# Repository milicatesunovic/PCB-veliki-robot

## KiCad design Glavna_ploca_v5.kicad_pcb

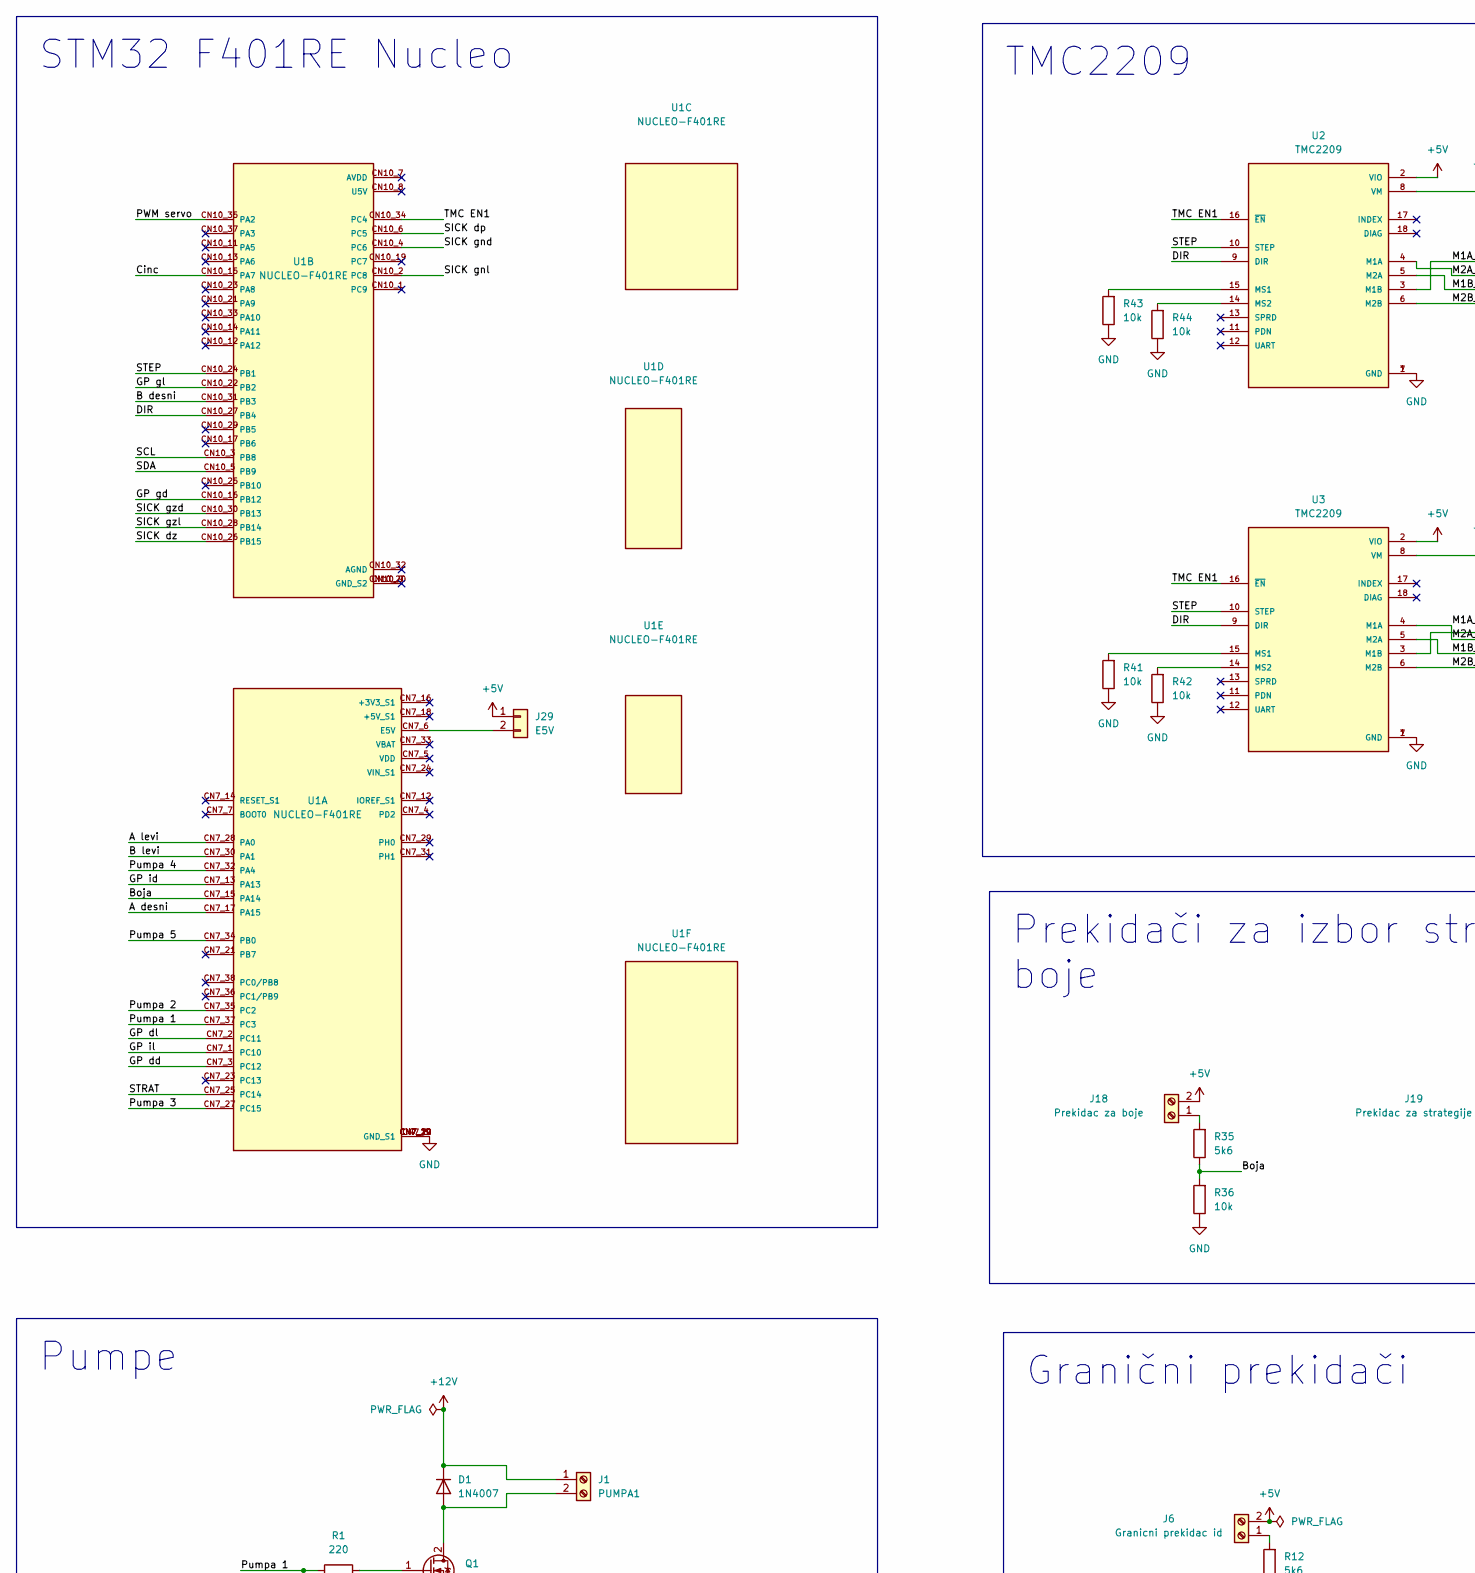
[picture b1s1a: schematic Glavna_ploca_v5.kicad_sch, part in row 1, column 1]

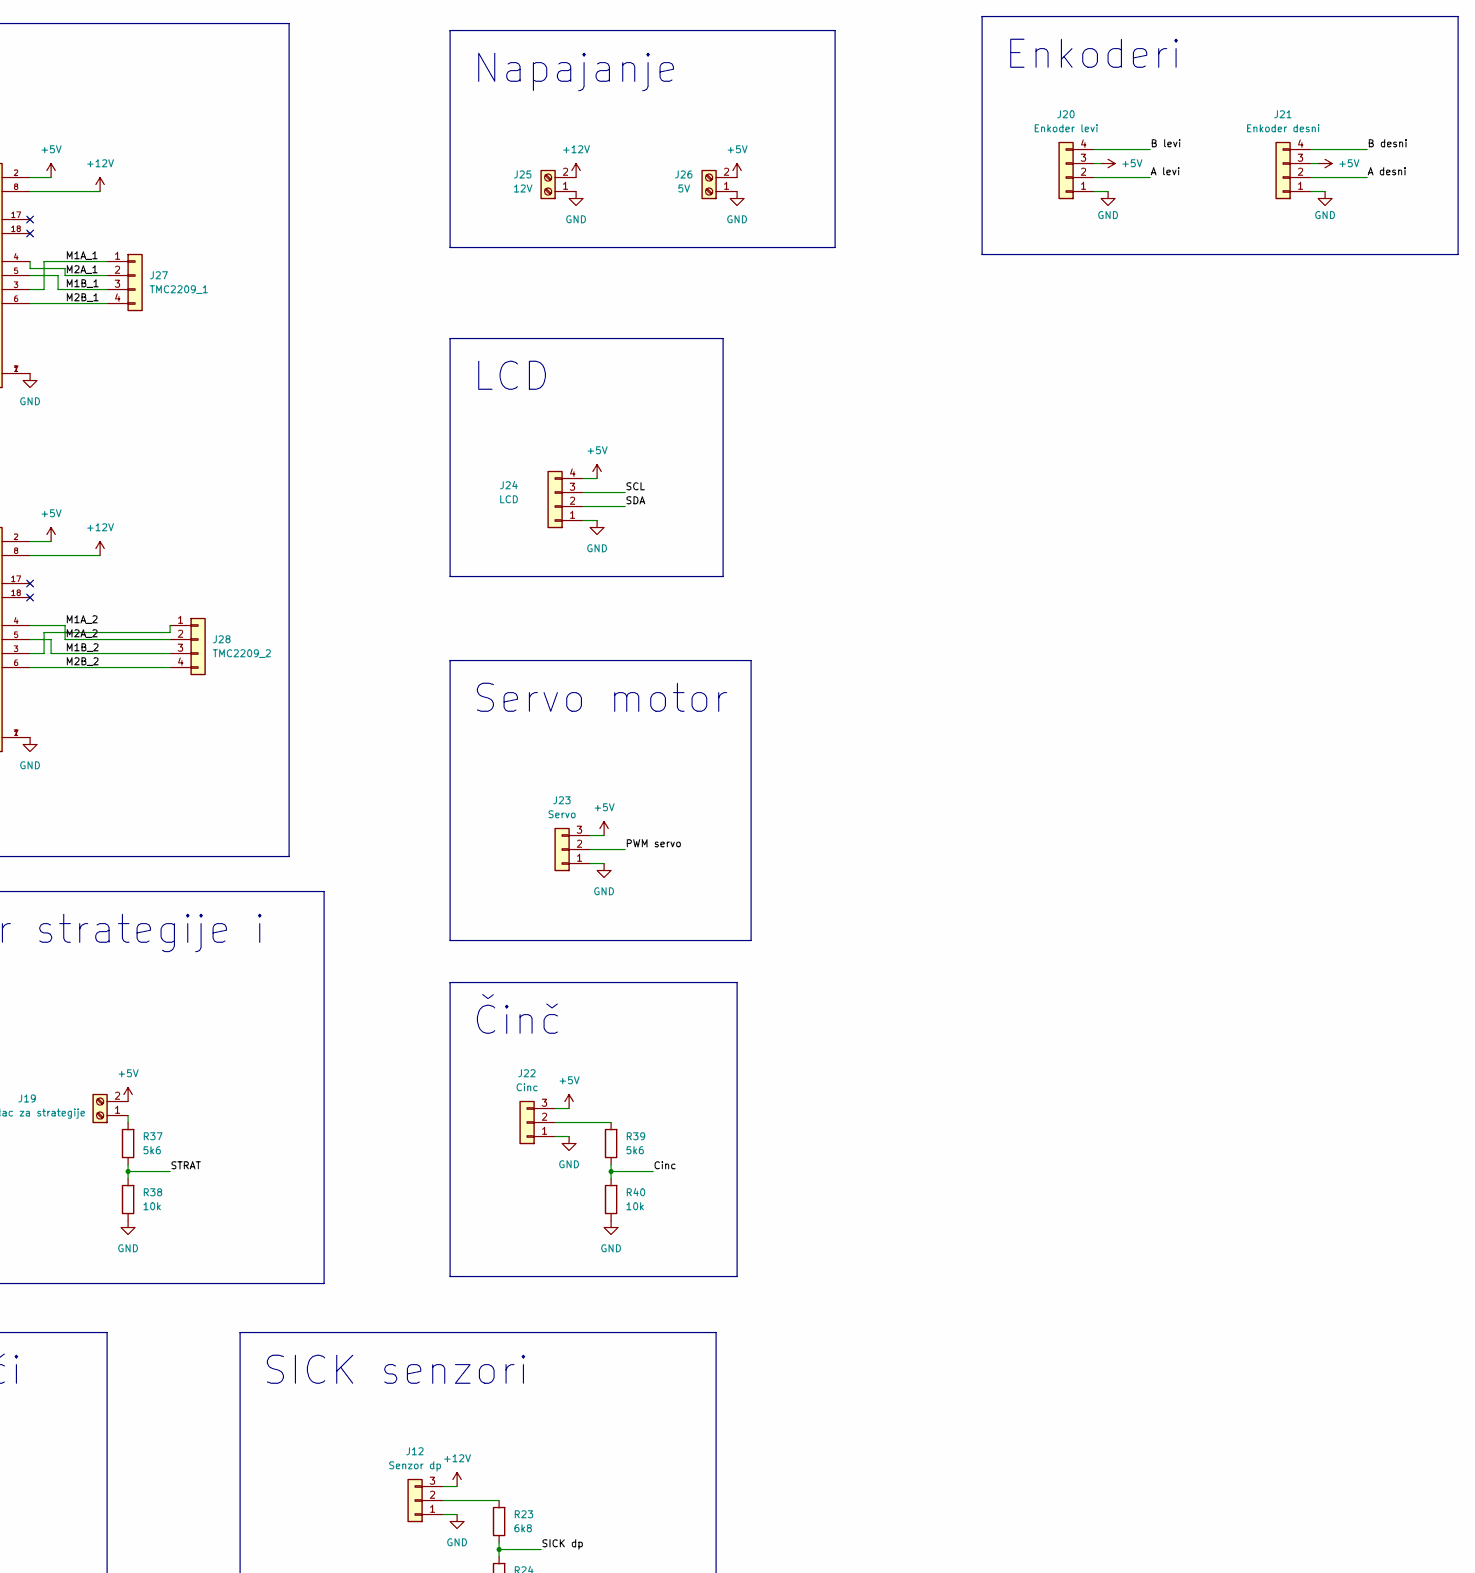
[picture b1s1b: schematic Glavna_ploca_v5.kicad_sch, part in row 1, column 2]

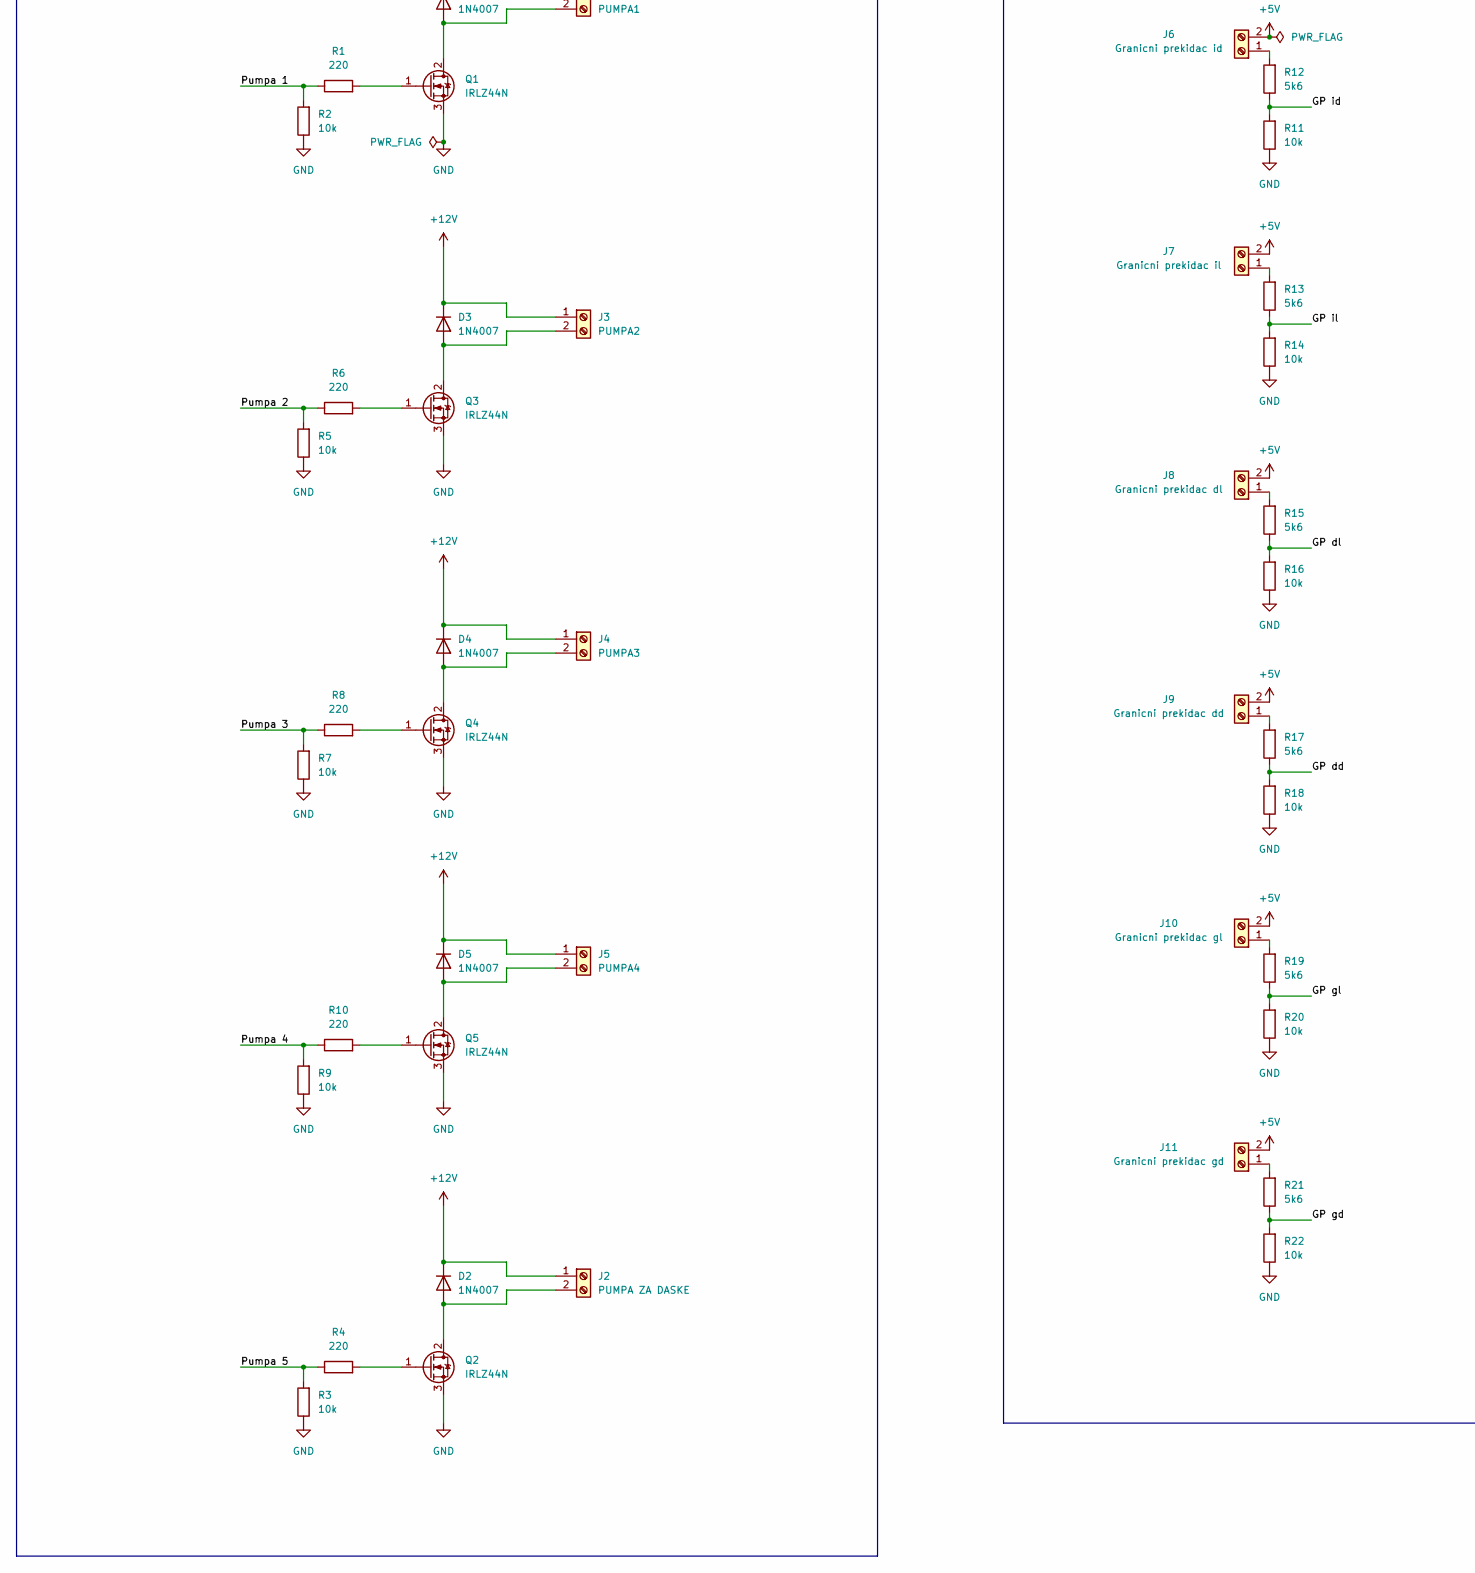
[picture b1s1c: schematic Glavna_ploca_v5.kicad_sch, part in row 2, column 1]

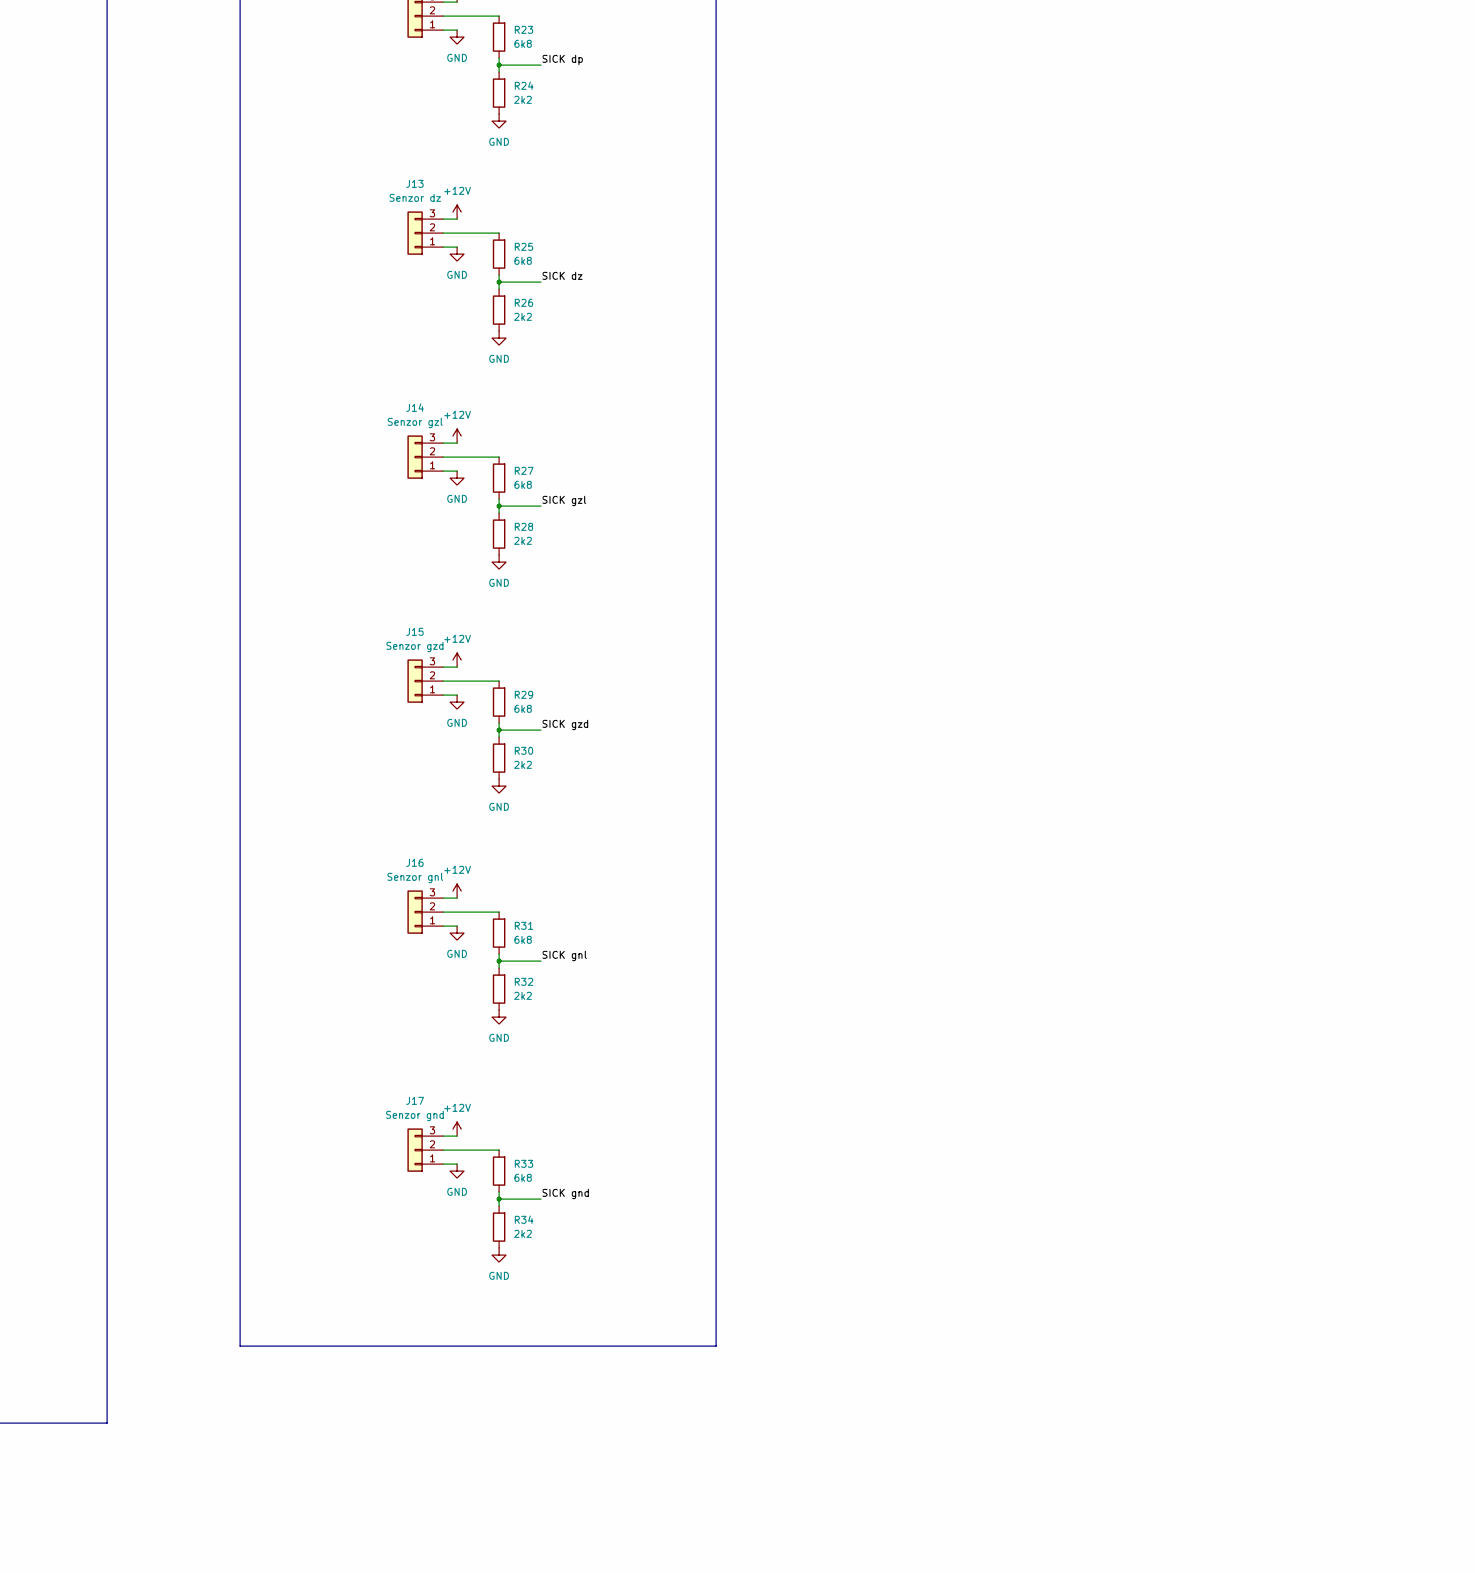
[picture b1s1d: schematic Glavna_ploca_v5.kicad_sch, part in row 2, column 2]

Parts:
D1, D2, D3, D4, D5: 1N4007; D_DO-41_SOD81_P10.16mm_Horizontal
J1: PUMPA1; TerminalBlock_bornier-2_P5.08mm
J2: PUMPA ZA DASKE; TerminalBlock_bornier-2_P5.08mm
J3: PUMPA2; TerminalBlock_bornier-2_P5.08mm
J4: PUMPA3; TerminalBlock_bornier-2_P5.08mm
J5: PUMPA4; TerminalBlock_bornier-2_P5.08mm
J6: Granicni prekidac id; TerminalBlock_bornier-2_P5.08mm
J7: Granicni prekidac il; TerminalBlock_bornier-2_P5.08mm
J8: Granicni prekidac dl; TerminalBlock_bornier-2_P5.08mm
J9: Granicni prekidac dd; TerminalBlock_bornier-2_P5.08mm
J10: Granicni prekidac gl; TerminalBlock_bornier-2_P5.08mm
J11: Granicni prekidac gd; TerminalBlock_bornier-2_P5.08mm
J12: Senzor dp; JST_XH_B3B-XH-A_1x03_P2.50mm_Vertical
J13: Senzor dz; JST_XH_B3B-XH-A_1x03_P2.50mm_Vertical
J14: Senzor gzl; JST_XH_B3B-XH-A_1x03_P2.50mm_Vertical
J15: Senzor gzd; JST_XH_B3B-XH-A_1x03_P2.50mm_Vertical
J16: Senzor gnl; JST_XH_B3B-XH-A_1x03_P2.50mm_Vertical
J17: Senzor gnd; JST_XH_B3B-XH-A_1x03_P2.50mm_Vertical
J18: Prekidac za boje; TerminalBlock_bornier-2_P5.08mm
J19: Prekidac za strategije; TerminalBlock_bornier-2_P5.08mm
J20: Enkoder levi; JST_XH_B4B-XH-A_1x04_P2.50mm_Vertical
J21: Enkoder desni; JST_XH_B4B-XH-A_1x04_P2.50mm_Vertical
J22: Cinc; JST_XH_B3B-XH-A_1x03_P2.50mm_Vertical
J23: Servo; JST_XH_B3B-XH-A_1x03_P2.50mm_Vertical
J24: LCD; JST_XH_B4B-XH-A_1x04_P2.50mm_Vertical
J25: 12V; TerminalBlock_bornier-2_P5.08mm
J26: 5V; TerminalBlock_bornier-2_P5.08mm
J27: TMC2209_1; JST_XH_B4B-XH-A_1x04_P2.50mm_Vertical
J28: TMC2209_2; JST_XH_B4B-XH-A_1x04_P2.50mm_Vertical
J29: E5V; JST_XH_B2B-XH-A_1x02_P2.50mm_Vertical
Q1, Q2, Q3, Q4, Q5: IRLZ44N; TO-220-3_Vertical
R1, R4, R6, R8, R10: 220; R_0805_2012Metric_Pad1.20x1.40mm_HandSolder
R2, R3, R5, R7, R9, R11, R14, R16, R18, R20, R22, R36, R38, R40, R41, R42, R43, R44: 10k; R_0805_2012Metric_Pad1.20x1.40mm_HandSolder
R12, R13, R15, R17, R19, R21, R35, R37, R39: 5k6; R_0805_2012Metric_Pad1.20x1.40mm_HandSolder
R23, R25, R27, R29, R31, R33: 6k8; R_0805_2012Metric_Pad1.20x1.40mm_HandSolder
R24, R26, R28, R30, R32, R34: 2k2; R_0805_2012Metric_Pad1.20x1.40mm_HandSolder
U1: NUCLEO-F401RE; ST_NUCLEO-F401RE; PARTREV 13
U2, U3: TMC2209; PARTREV 1.20

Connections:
+5V: J6.2, J7.2, J8.2, J9.2, J10.2, J11.2, J18.2, J19.2, J20.3, J21.3, J22.3, J23.3, J24.4, J26.2, J29.1, U2.2 (VIO), U3.2 (VIO)
+12V: D1.1 (K), D2.1 (K), D3.1 (K), D4.1 (K), D5.1 (K), J1.1, J2.1, J3.1, J4.1, J5.1, J12.3, J13.3, J14.3, J15.3, J16.3, J17.3, J25.2, U2.8 (VM), U3.8 (VM)
/A desni: J21.2, U1.CN7_17 (PA15)
/A levi: J20.2, U1.CN7_28 (PA0)
/B desni: J21.4, U1.CN10_31 (PB3)
/B levi: J20.4, U1.CN7_30 (PA1)
/Boja: R35.1, R36.2, U1.CN7_15 (PA14)
/Cinc: R39.1, R40.2, U1.CN10_15 (PA7)
/DIR: U1.CN10_27 (PB4), U2.9 (DIR), U3.9 (DIR)
/GP dd: R17.1, R18.2, U1.CN7_3 (PC12)
/GP dl: R15.1, R16.2, U1.CN7_2 (PC11)
/GP gd: R21.1, R22.2, U1.CN10_16 (PB12)
/GP gl: R19.1, R20.2, U1.CN10_22 (PB2)
/GP id: R11.2, R12.1, U1.CN7_13 (PA13)
/GP il: R13.1, R14.2, U1.CN7_1 (PC10)
/M1A_1: J27.1, U2.3 (M1B)
/M1A_2: J28.2, U3.4 (M1A)
/M1B_1: J27.3, U2.5 (M2A)
/M1B_2: J28.3, U3.5 (M2A)
/M2A_1: J27.2, U2.4 (M1A)
/M2B_1: J27.4, U2.6 (M2B)
/M2B_2: J28.4, U3.6 (M2B)
/PWM servo: J23.2, U1.CN10_35 (PA2)
/Pumpa 1: R1.1, R2.2, U1.CN7_37 (PC3)
/Pumpa 2: R5.2, R6.1, U1.CN7_35 (PC2)
/Pumpa 3: R7.2, R8.1, U1.CN7_27 (PC15)
/Pumpa 4: R9.2, R10.1, U1.CN7_32 (PA4)
/Pumpa 5: R3.2, R4.1, U1.CN7_34 (PB0)
/SCL: J24.3, U1.CN10_3 (PB8)
/SDA: J24.2, U1.CN10_5 (PB9)
/SICK dp: R23.1, R24.2, U1.CN10_6 (PC5)
/SICK dz: R25.1, R26.2, U1.CN10_26 (PB15)
/SICK gnd: R33.1, R34.2, U1.CN10_4 (PC6)
/SICK gnl: R31.1, R32.2, U1.CN10_2 (PC8)
/SICK gzd: R29.1, R30.2, U1.CN10_30 (PB13)
/SICK gzl: R27.1, R28.2, U1.CN10_28 (PB14)
/STEP: U1.CN10_24 (PB1), U2.10 (STEP), U3.10 (STEP)
/STRAT: R37.1, R38.2, U1.CN7_25 (PC14)
/TMC EN1: U1.CN10_34 (PC4), U2.16 (~EN), U3.16 (~EN)
GND: J12.1, J13.1, J14.1, J15.1, J16.1, J17.1, J20.1, J21.1, J22.1, J23.1, J24.1, J25.1, J26.1, Q1.3 (S), Q2.3 (S), Q3.3 (S), Q4.3 (S), Q5.3 (S), R2.1, R3.1, R5.1, R7.1, R9.1, R11.1, R14.1, R16.1, R18.1, R20.1, R22.1, R24.1, R26.1, R28.1, R30.1, R32.1, R34.1, R36.1, R38.1, R40.1, R41.1, R42.1, R43.1, R44.1, U1.CN7_8 (GND_S1), U1.CN7_19 (GND_S1), U1.CN7_20 (GND_S1), U1.CN7_22 (GND_S1), U2.1 (GND), U2.7 (GND), U3.1 (GND), U3.7 (GND)
unnamed: D1.2 (A), J1.2, Q1.2 (D)
unnamed: D2.2 (A), J2.2, Q2.2 (D)
unnamed: D3.2 (A), J3.2, Q3.2 (D)
unnamed: D4.2 (A), J4.2, Q4.2 (D)
unnamed: D5.2 (A), J5.2, Q5.2 (D)
unnamed: J6.1, R12.2
unnamed: J7.1, R13.2
unnamed: J8.1, R15.2
unnamed: J9.1, R17.2
unnamed: J10.1, R19.2
unnamed: J11.1, R21.2
unnamed: J12.2, R23.2
unnamed: J13.2, R25.2
unnamed: J14.2, R27.2
unnamed: J15.2, R29.2
unnamed: J16.2, R31.2
unnamed: J17.2, R33.2
unnamed: J18.1, R35.2
unnamed: J19.1, R37.2
unnamed: J22.2, R39.2
unnamed: J28.1, U3.3 (M1B)
unnamed: J29.2, U1.CN7_6 (E5V)
unnamed: Q1.1 (G), R1.2
unnamed: Q2.1 (G), R4.2
unnamed: Q3.1 (G), R6.2
unnamed: Q4.1 (G), R8.2
unnamed: Q5.1 (G), R10.2
unnamed: R43.2, U2.15 (MS1)
unnamed: R44.2, U2.14 (MS2)
unnamed: R41.2, U3.15 (MS1)
unnamed: R42.2, U3.14 (MS2)

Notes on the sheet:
TMC2209
SICK senzori
Granični prekidači
Enkoderi
Prekidači za izbor strategije i boje
Pumpe
Servo motor
STM32 F401RE Nucleo
Činč
Napajanje
LCD

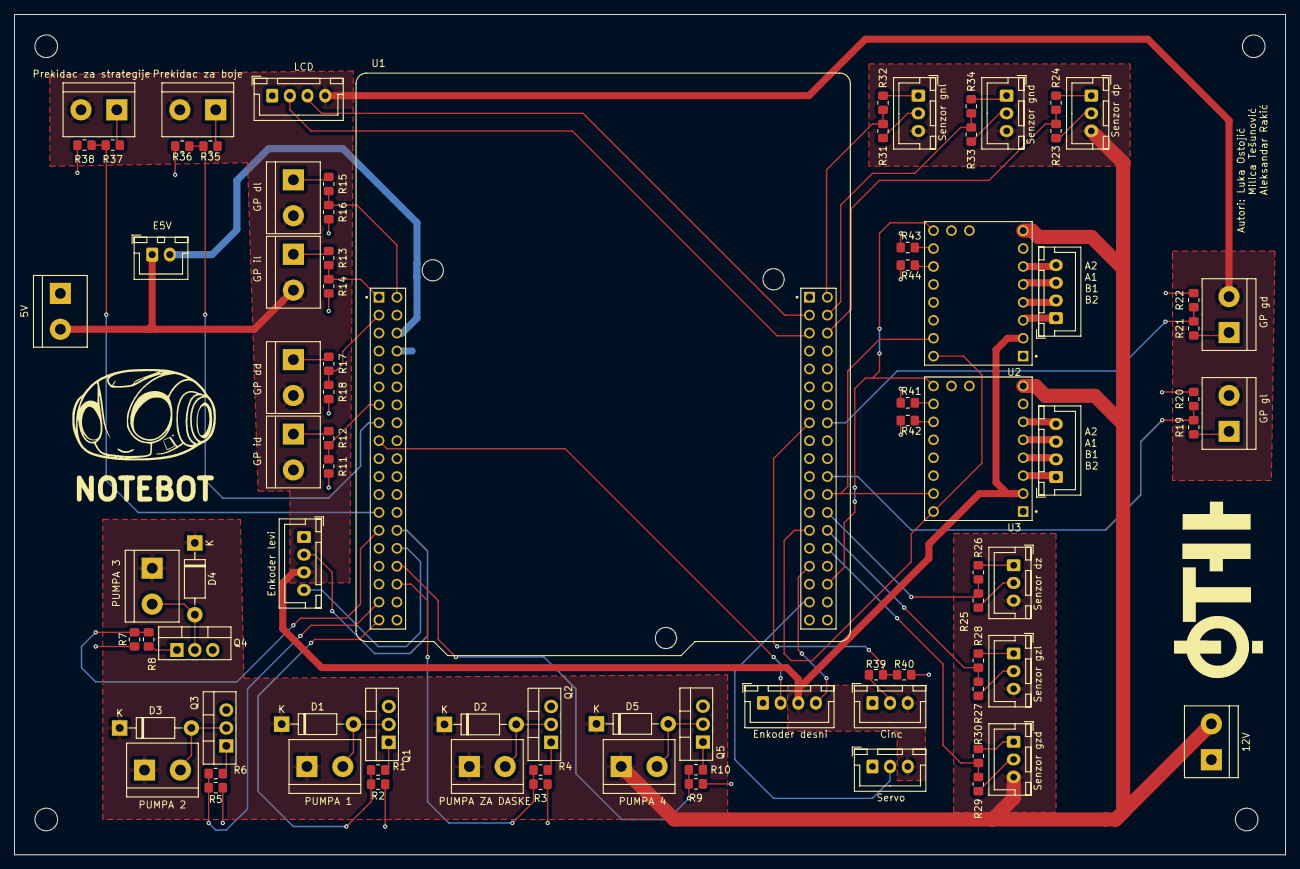
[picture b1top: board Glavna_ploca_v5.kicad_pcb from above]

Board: 2 copper layers, 180.0 x 119.0 mm, 86 parts (0 on the bottom side), 71 nets.

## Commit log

2025-02-12 prvi commit
2025-02-12 pcb sa napajanjem
2025-02-14 konacna ploca
2025-02-16 dodati nazivi
2025-02-17 dodate rupe
2025-02-17 konacno
2025-02-17 potpisana
